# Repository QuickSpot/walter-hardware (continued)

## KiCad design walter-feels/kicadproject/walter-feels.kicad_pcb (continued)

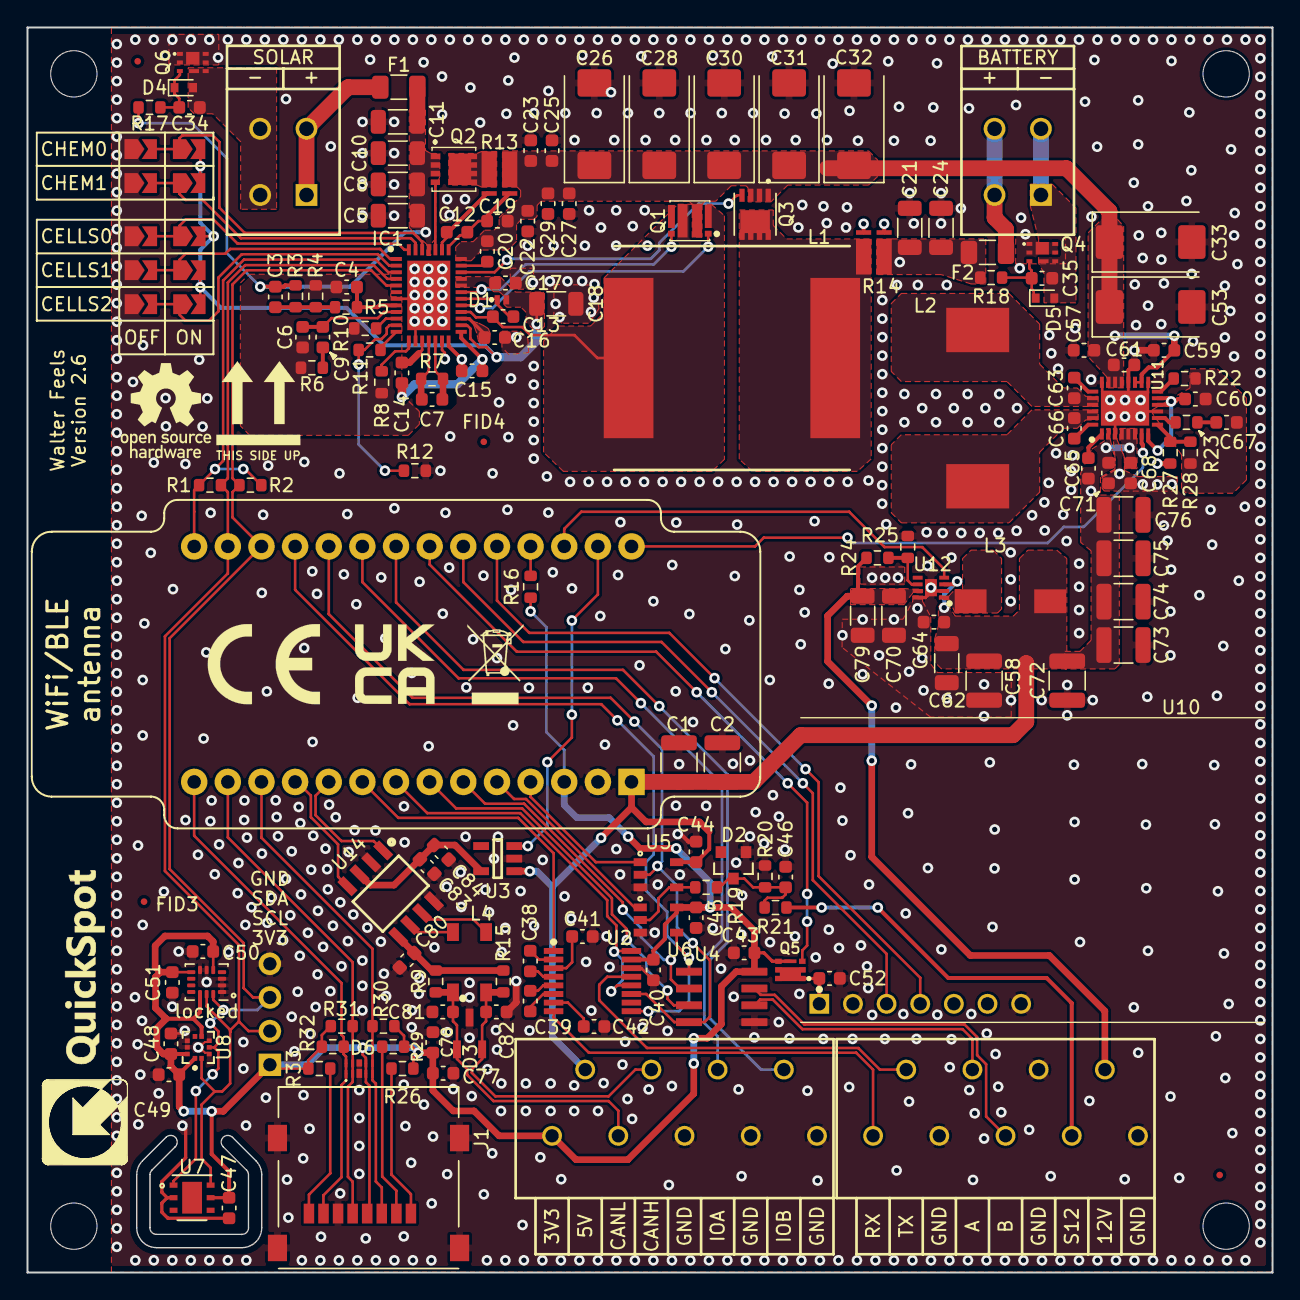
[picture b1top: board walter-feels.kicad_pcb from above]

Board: 4 copper layers, 94.0 x 94.0 mm, 167 parts (0 on the bottom side), 104 nets.

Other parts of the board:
FID1, FID2, FID3, FID4: Fiducial; Fiducial_0.5mm_Mask1mm
H1, H2, H3, H4: MountingHole; MountingHole_2.7mm_M2.5_ISO14580
locked: LSM6DSM; LGA-14_3x2.5mm_P0.5mm_LayoutBorder3x4y

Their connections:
+3.3V: locked.5 (VDDIO), locked.8 (VDD), locked.12 (CS); also elsewhere on the board
GND: locked.1 (SDO/SA0), locked.2 (SDX), locked.3 (SCX), locked.6 (GND), locked.7 (GND); also elsewhere on the board
I2C_SCL: locked.13 (SCL); also elsewhere on the board
I2C_SDA: locked.14 (SDA); also elsewhere on the board

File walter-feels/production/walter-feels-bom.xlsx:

Designator | Value | Description | Footprint | Qty | Manufacturer | Part Number
C1, C2, C58, C72, C73, C74, C75, C76 | 100µF | 100μF ±20%, 6.3V, X5R, 1210 MLCC | 1210 | 8 | Any | Any
C3 | 2200pF | 2200pF ±10%, 50V, X7R, 0603 MLCC | 0603 | 1 | Any | Any
C4 | 100pF | 100pF ±5%, 50V, C0G, 0603 MLCC | 0603 | 1 | Any | Any
C5, C8, C10, C11, C18, C21, C24, C62, C70, C79 | 10µF | 10µF ±10%, 50V, X5R, 1206 MLCC | 1206 | 10 | Any | Any
C6, C34, C35 | 10nF | 10nF ±10%, 50V, X7R, 0603 MLCC | 0603 | 3 | Any | Any
C7, C17, C22, C38, C39, C40, C41, C42, C43, C44, C45, C47, C48, C49, C50, C51, 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 | 0.1µF | 0.1µF ±10%, 50V, X7R, 0603 MLCC | 0603 | 24 | Any | Any
C9, C63, C66 | 0.22μF | 0.22μF ±10%, 25V, X7R, 0603 MLCC | 0603 | 3 | Any | Any
C12, C15 | 1000pF | 1000pF ±10%, 50V, X7R, 0603 MLCC | 0603 | 2 | Any | Any
C13 | 0.470µF | 0.470µF ±10%, 25V, X7R, 0603 MLCC | 0603 | 1 | Any | Any
C14, C20 | 0.33μF | 0.33μF ±10%, 25V, X7R, 0603 MLCC | 0603 | 2 | Any | Any
C16 | 2.2μF | 2.2μF ±10%, 16V, X5R, 0603 MLCC | 0603 | 1 | Any | Any
C19, C23, C25, C27, C29, C59, C77 | 1μF | 1μF ±10%, 50V, X5R, 0603 MLCC | 0603 | 7 | Any | Any
C26, C28, C30, C31, C32, C33, C53 | 33µF, 35V | 33μF ±20%, 35V, Polymer Tantalum Capacitor | 2917 | 7 | Kyocera AVX | TCJE336M035R0055
C46 | 33nF | 33nF ±10%, 50V, X7R, 0603 MLCC | 0603 | 1 | Any | Any
C60 | 4.7μF | 4.7μF ±10%, 16V, X5R, 0603 MLCC | 0603 | 2 | Any | Any
C65 | 22nF | 22nF ±10%, 50V, X7R, 0603 MLCC | 0603 | 1 | Any | Any
C67 | 1200pF | 1200pF ±10%, 50V, X7R, 0603 MLCC | 0603 | 1 | Any | Any
C80 | 4700pF | 4700pF ±10%, 50V, X7R, 0603 MLCC | 0603 | 1 | Any | Any
C81, C82 | 18pF | 18pF ±5%, 50V, C0G, 0603 MLCC | 0603 | 2 | Any | Any
D1 |  | 80V, 0.3A, Fast switching diode | DFN-2 | 1 | Diodes Incorporated | 1N4448HLP-7
D2 | 5.6V | 5.6V, 225mW, Zener diode | SOT-23 | 1 | Onsemi | BZX84C5V6LT1G
D3 |  | 25V, 230W, CAN-bus TVS diode | SOT-23 | 1 | STMicroelectronics | ESDCAN01-2BLY
D4, D5 | 8.2V | 8.2V, 0.2W, Zener diode | SOD-523 | 2 | Onsemi | MM5Z8V2T1G
D6 |  | TVS Diode array | 10-UFDFN | 1 | Diodes Incorporated | D3V3X4U10LP-7
F1, F2 | 5A Slow | 5A, 32VDC, Slow, 1206 Fuse | 1206 | 2 | Littelfuse | 0407005.WR.
IC1 |  | Multichemistry buck battery charger controller with digital telemetry | QFN-38 | 1 | Analog Devices | LTC4015EUHF#PBF
J1 |  | Micro-SD card slot | SMT | 1 | Wurth Electronics | 693072010801
J2, J3 |  | 1 row, 2 position, Spring clamp terminal block | THT | 2 | Phoenix Contact | 1071010
J4, J5 |  | 1 row, 9 position, Spring clamp terminal block | THT | 2 | Phoenix Contact | 1990070
J6 |  | 1 row, 4 position, 2.54mm male THT pin header | THT | 1 | Any | Any
J7, J8 |  | 1 row, 14 position, 8.5H, 2.54mm female THT pin header receptacle | THT | 2 | Any | Any
L1 | 10μH | 10μH ±20%, 17A Irms, 25A Isat, 11.6mΩ DCR, Power inductor | SMT | 1 | Bourns | SRP1770C-100M
L2 | 3.3μH | 3.3μH ±20%, 18A Irms, 30A Isat, 5.7mΩ DCR, Power inductor | SMT | 1 | Pulse Elec | PM4343.332NLT
L3 | 10μH | 10μH ±20%, 2.7A Irms, 1.9A Isat, 48mΩ DCR, Power inductor | SMT | 1 | Bourns | SRR7045-100M
L4 |  | 2.8kΩ @ 10MHz, 51μH @ 100kHz, 1Ω DCR, common mode filter | SMT | 1 | TDK | ACT45B-510-2P-TL003
Q1 |  | 40V, 12A, 10mΩ, dual N-channel power MOSFET | Power-33 | 1 | Onsemi | FDMC8030
Q2 |  | 40V, 14A, 9.7mΩ, N-channel MOSFET | Power-33 | 1 | Onsemi | FDMC8327L
Q3 |  | 40V, 18A, 25mΩ, P-channel MOSFET | PowerPAK-1212-8 | 1 | Vishay Intertech | SI7611DN-T1-GE3
Q4, Q6 |  | 30V, 25A, 15.1mΩ, N-channel MOSFET | 6-WSON | 2 | Texas Instruments | CSD17318Q2
Q5 |  | 20V, 9A, 16mΩ, P-channel MOSFET | UDFN-2020-6 | 1 | Diodes Incorporated | DMP2021UFDE-7
R1, R2 | 45.3kΩ | 45.3kΩ ±1%, 100mW, 50V, 0603 resistor | 0603 | 2 | Any | Any
R3, R23 | 64.9kΩ | 64.9kΩ ±1%, 100mW, 50V, 0603 resistor | 0603 | 2 | Any | Any
R4, R5, R8, R11, R26, R29, R30, R31, R32, R33 | 10kΩ | 10kΩ ±1%, 100mW, 50V, 0603 resistor | 0603 | 10 | Any | Any
R6 | 200Ω | 200Ω ±1%, 100mW, 50V, 0603 resistor | 0603 | 1 | Any | Any
R7 | 301kΩ | 301kΩ ±1%, 100mW, 50V, 0603 resistor | 0603 | 1 | Any | Any
R9, R15 | 60.4Ω | 60.4Ω ±1%, 100mW, 50V, 0603 resistor | 0603 | 2 | Any | Any
R10 | 95.3kΩ | 95.3kΩ ±1%, 100mW, 50V, 0603 resistor | 0603 | 1 | Any | Any
R12 | 10kΩ | 10kΩ ±1%, 100mW, 50V, 3380K ±1%, 0603 NTC resistor | 0603 | 1 | Any | Any
R13 | 0.003Ω | 0.003Ω ±1%, 1W, 1206 current sensing resistor | 1206 | 1 | Susumu | KRL3216T4-M-R003-F-T1
R14 | 0.004Ω | 0.004Ω ±1%, 1W, 1206 current sensing resistor | 1206 | 1 | Susumu | KRL3216T4-M-R004-F-T1
R16, R17, R18 | 8.2MΩ | 8.2MΩ ±1%, 100mW, 50V, 0603 resistor | 0603 | 3 | Any | Any
R19, R21 | 510Ω | 510Ω ±1%, 100mW, 50V, 0603 resistor | 0603 | 2 | Any | Any
R20 | 200kΩ | 200kΩ ±1%, 100mW, 50V, 0603 resistor | 0603 | 1 | Any | Any
R22 | 75kΩ | 75kΩ ±1%, 100mW, 50V, 0603 resistor | 0603 | 1 | Any | Any
R24 | 3.48MΩ | 3.48MΩ ±1%, 100mW, 50V, 0603 resistor | 0603 | 1 | Any | Any
R25 | 402kΩ | 402kΩ ±1%, 100mW, 50V, 0603 resistor | 0603 | 1 | Any | Any
R27 | 1MΩ | 1MΩ ±1%, 63mW, 50V, 0603 resistor | 0603 | 1 | Any | Any
R28 | 187kΩ | 187kΩ ±1%, 100mW, 50V, 0603 resistor | 0603 | 1 | Any | Any
U2 |  | 250kbps, RS232 transceiver | TSSOP-16 | 1 | Texas Instruments | MAX3221IPWR
U3 |  | 2.5V-5.5V, 0.5A, 170mΩ power distribution switch | SOT-23-5 | 1 | Microchip | MIC2005A-2YM5-TR
U4 |  | 50Mbps, RS485 transceiver | SOIC-8 | 1 | Texas Instruments | THVD1450DR
U5, U6 |  | Level shifter | SOT-23-5 | 2 | Texas Instruments | SN74LV1T126DBVR
U7 |  | Temperature and humidity sensor | WSON-6 | 1 | Texas Instruments | HDC1080DMBR
U8 |  | Barometric pressure sensor | LGA-10 | 1 | STMicroelectronics | LPS22HBTR
U9 |  | Accelerometer and Gyroscope | LGA-14 | 1 | STMicroelectronics | LSM6DSM
U11 |  | 2.5V-26V, low Iq, DC-DC buck/boost converter | LQFN-28 | 1 | Analog Devices | LT3120JV#PBF
U12 |  | 1.8V-5.5V, 1A, DC-DC boost converter | DFN-8-EP | 1 | Analog Devices | MAX17291ATA+T
U14 |  | 1Mbps CAN-bus transceiver | SOIC-8 | 1 | Texas Instruments | SN65HVDA1050AQDRQ1

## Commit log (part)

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2023-04-12 Initial import
2023-04-12 Updated gitignore
2023-05-11 Fixed missing pad 20 in footprints
2023-07-10 Updated datasheet with the correct pinout and pin descriptions
2023-07-10 Fixed mirrored pinout on Walter symbol in KiCAD
2023-09-14 Updated datasheet to v1.4
2023-09-14 Added SFU update information
2023-10-06 Initial draft release of the Walter Feels expansion board
2023-10-13 Updated Walter schematic to v1.5 and updated Walter Feels to version 2.1
2024-03-27 [walter_datasheet.tex] Fix typo: "not" --> "note"
2024-03-27 Added final V1.6 schematic
    The schematic of final version v1.6 was not yet added to the repository.
2024-05-31 Added extra PCB receptacles for Walter
2024-12-05 Updated Walter Feels to V2.3
2025-02-12 Updated to version 2.4
2025-05-19 add 2D laser cut outlines and readme for housing prototyping
2025-12-19 Fixed pin 10 (IO40), it was set as input only but it is bidirectional
2026-01-13 Updated Walter Feels project to version 2.6
2026-06-22 Updated the datasheet
